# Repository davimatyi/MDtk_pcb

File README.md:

# MDtk board desing
This is an Autodesk EAGLE project, it contains the design files of a printed circuit board for the MDtk programmable numeric keypad, designed by me.

# Design

# Hardware
It uses Cherry MX-style switches, a 0.96" OLED display, and an STM32F411CEU6 development board.

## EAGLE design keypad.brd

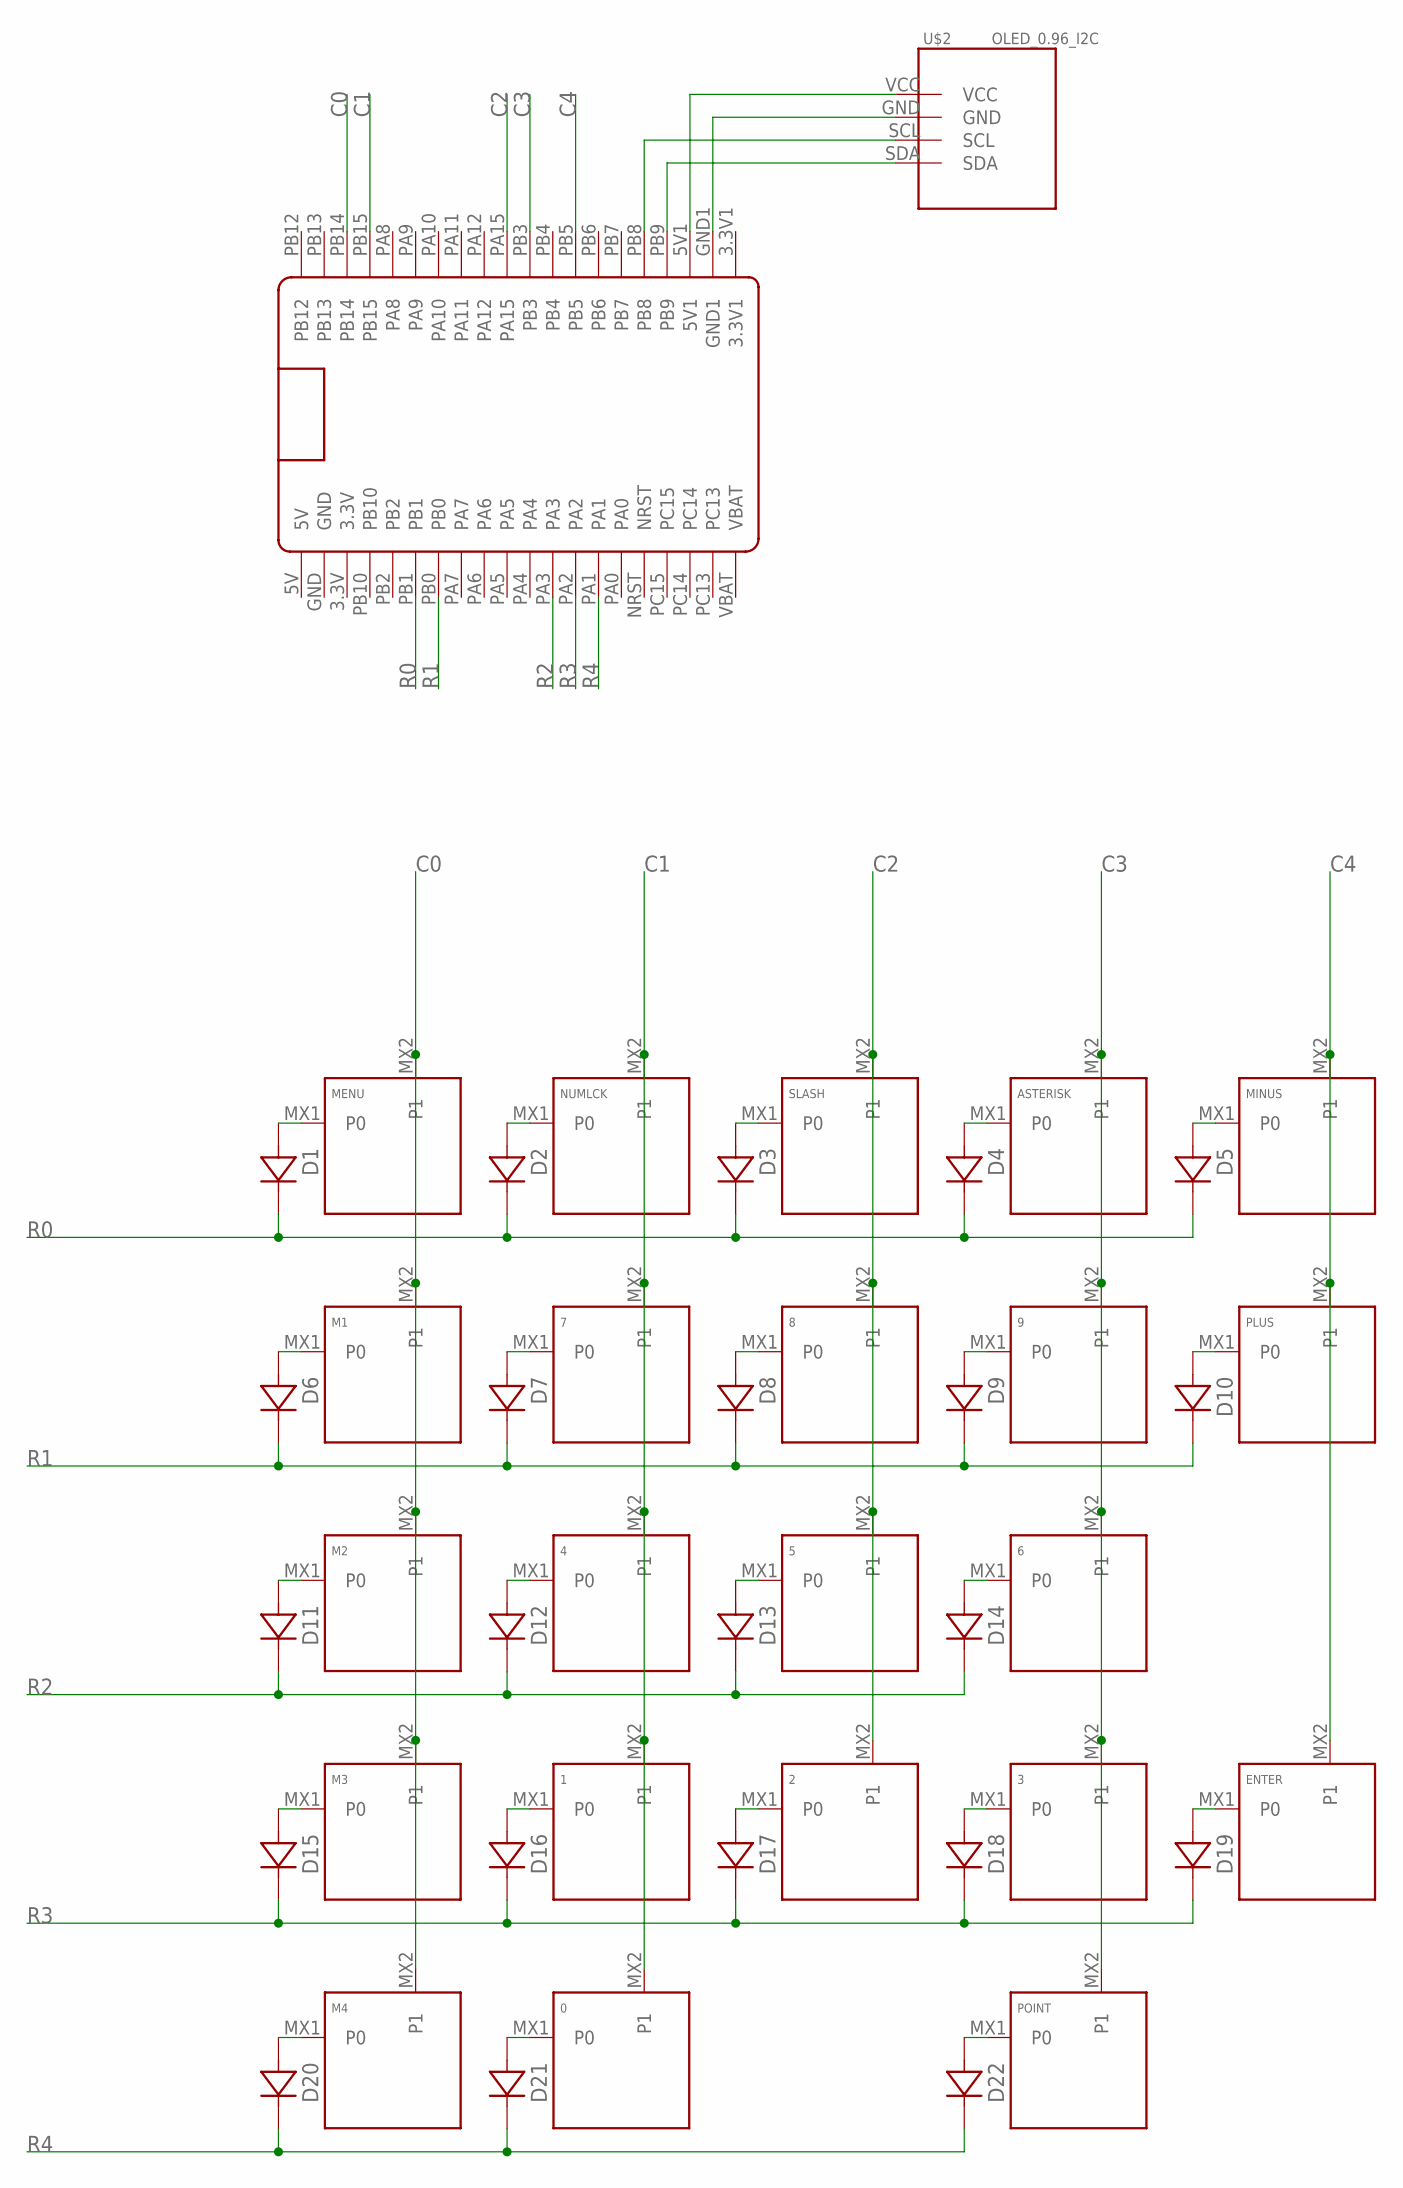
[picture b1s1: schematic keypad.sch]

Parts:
0: KEYSWITCH-PLAIN-MX-2U-FLIPPED; MX-2U-FLIPPED
1, 2, 3, 4, 5, 6, 7, 8, 9: KEYSWITCH-PLAIN-MX-1U; MX-1U
ASTERISK: KEYSWITCH-PLAIN-MX-1U; MX-1U
D1, D2, D3, D4, D5, D6, D7, D8, D9, D10, D11, D12, D13, D14, D15, D16, D17, D18, D19, D20, D21, D22: DIODE-SOD-123; SOD-123
ENTER: KEYSWITCH-PLAIN-MX-2U-ROTATED; MX-2U-ROTATED
M1, M2, M3, M4: KEYSWITCH-PLAIN-MX-1U; MX-1U
MENU: KEYSWITCH-PLAIN-MX-1U; MX-1U
MINUS: KEYSWITCH-PLAIN-MX-1U; MX-1U
NUMLCK: KEYSWITCH-PLAIN-MX-1U; MX-1U
PLUS: KEYSWITCH-PLAIN-MX-2U-ROTATED; MX-2U-ROTATED
POINT: KEYSWITCH-PLAIN-MX-1U; MX-1U
SLASH: KEYSWITCH-PLAIN-MX-1U; MX-1U
U$1: BLACK_PILL
U$2: OLED_0.96_I2C

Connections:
5V: U$1.5V
C0: M1.MX2 (P1), M2.MX2 (P1), M3.MX2 (P1), M4.MX2 (P1), MENU.MX2 (P1), U$1.PB14
C1: 0.MX2 (P1), 1.MX2 (P1), 4.MX2 (P1), 7.MX2 (P1), NUMLCK.MX2 (P1), U$1.PB15
C2: 2.MX2 (P1), 5.MX2 (P1), 8.MX2 (P1), SLASH.MX2 (P1), U$1.PA15
C3: 3.MX2 (P1), 6.MX2 (P1), 9.MX2 (P1), ASTERISK.MX2 (P1), POINT.MX2 (P1), U$1.PB3
C4: ENTER.MX2 (P1), MINUS.MX2 (P1), PLUS.MX2 (P1), U$1.PB5
unnamed: D1.A, MENU.MX1 (P0)
unnamed: D2.A, NUMLCK.MX1 (P0)
unnamed: D3.A, SLASH.MX1 (P0)
unnamed: ASTERISK.MX1 (P0), D4.A
unnamed: D5.A, MINUS.MX1 (P0)
unnamed: D6.A, M1.MX1 (P0)
unnamed: 7.MX1 (P0), D7.A
unnamed: 8.MX1 (P0), D8.A
unnamed: 9.MX1 (P0), D9.A
unnamed: D10.A, PLUS.MX1 (P0)
unnamed: D11.A, M2.MX1 (P0)
unnamed: 4.MX1 (P0), D12.A
unnamed: 5.MX1 (P0), D13.A
unnamed: 6.MX1 (P0), D14.A
unnamed: D15.A, M3.MX1 (P0)
unnamed: 1.MX1 (P0), D16.A
unnamed: 2.MX1 (P0), D17.A
unnamed: 3.MX1 (P0), D18.A
unnamed: D19.A, ENTER.MX1 (P0)
unnamed: D20.A, M4.MX1 (P0)
unnamed: 0.MX1 (P0), D21.A
unnamed: D22.A, POINT.MX1 (P0)
unnamed: U$1.5V1, U$2.VCC
unnamed: U$1.GND1, U$2.GND
unnamed: U$1.PB9, U$2.SDA
unnamed: U$1.PB8, U$2.SCL
R0: D1.C, D2.C, D3.C, D4.C, D5.C, U$1.PB1
R1: D6.C, D7.C, D8.C, D9.C, D10.C, U$1.PB0
R2: D11.C, D12.C, D13.C, D14.C, U$1.PA3
R3: D15.C, D16.C, D17.C, D18.C, D19.C, U$1.PA2
R4: D20.C, D21.C, D22.C, U$1.PA1

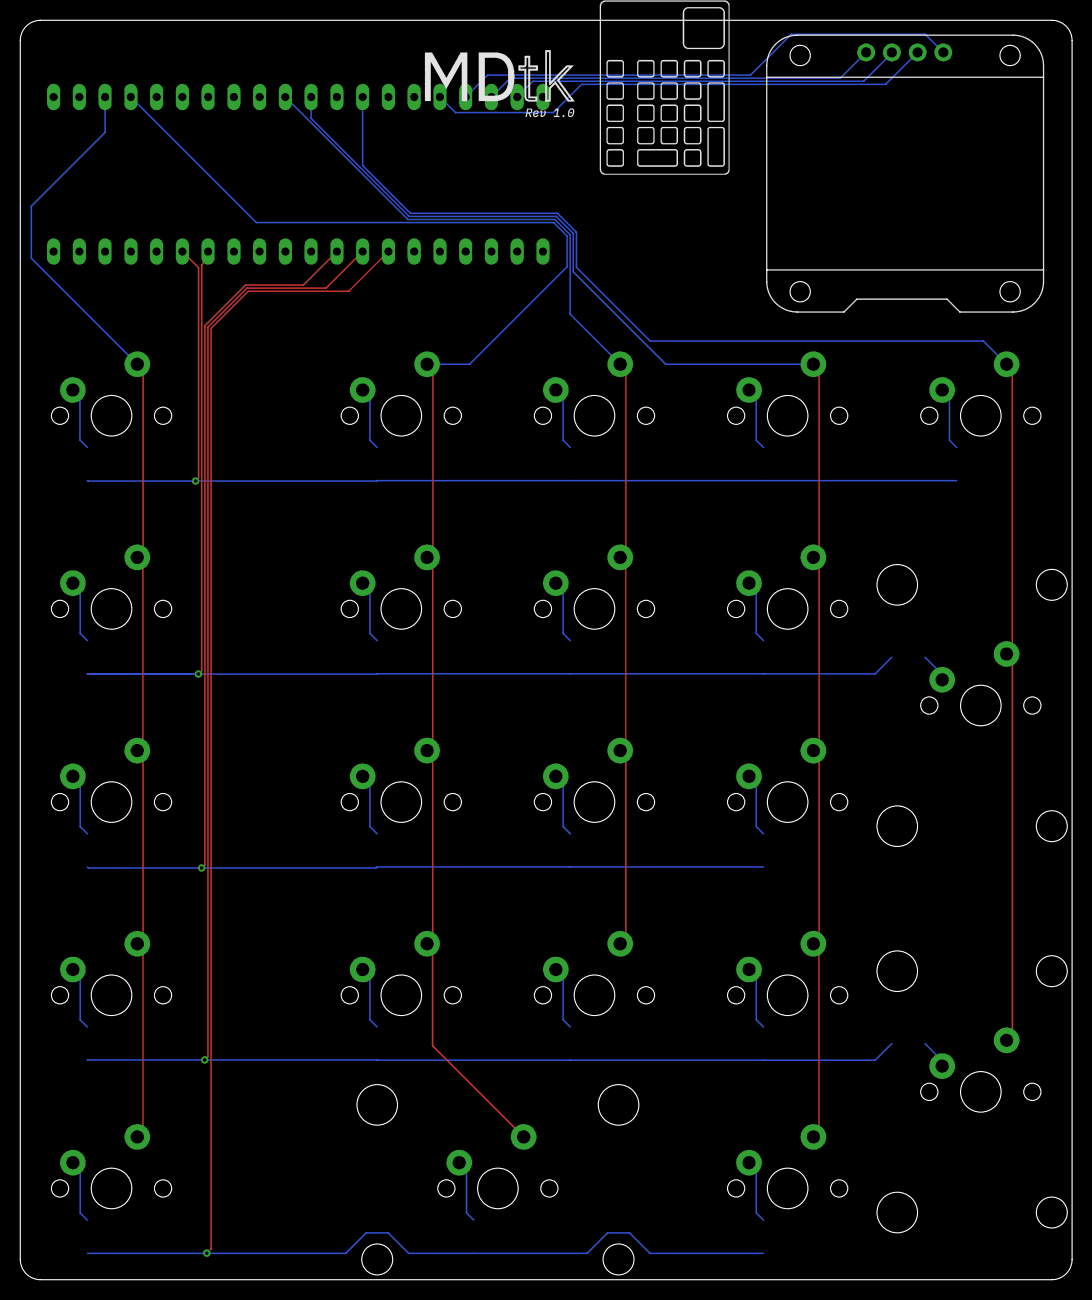
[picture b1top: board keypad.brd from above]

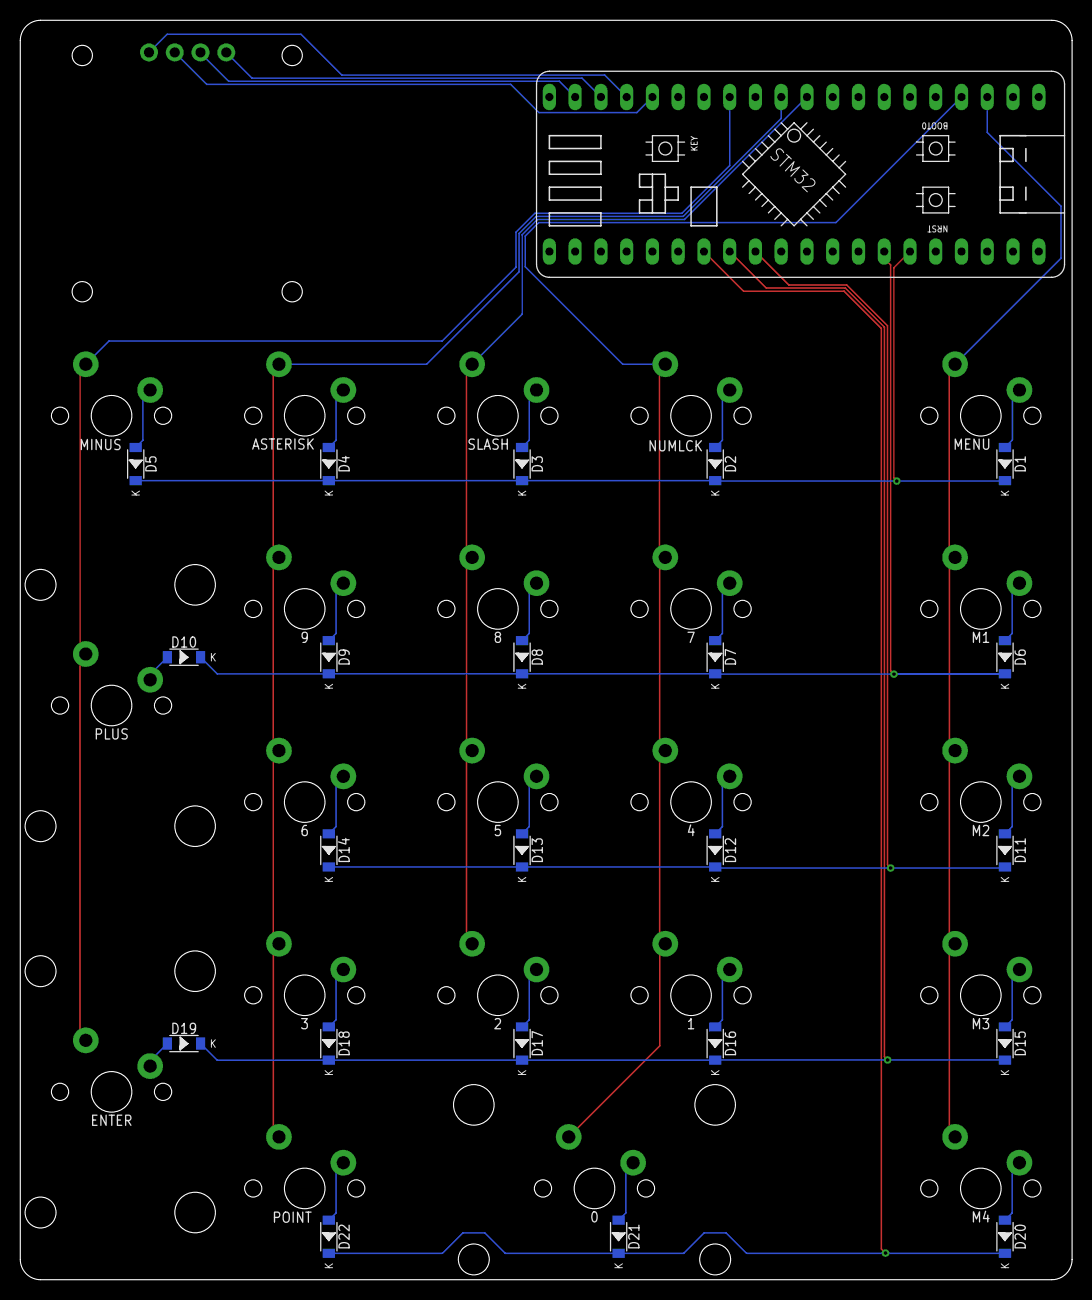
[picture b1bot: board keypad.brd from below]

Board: 2 copper layers, 103.7 x 124.2 mm, 46 parts (23 on the bottom side), 36 nets.
